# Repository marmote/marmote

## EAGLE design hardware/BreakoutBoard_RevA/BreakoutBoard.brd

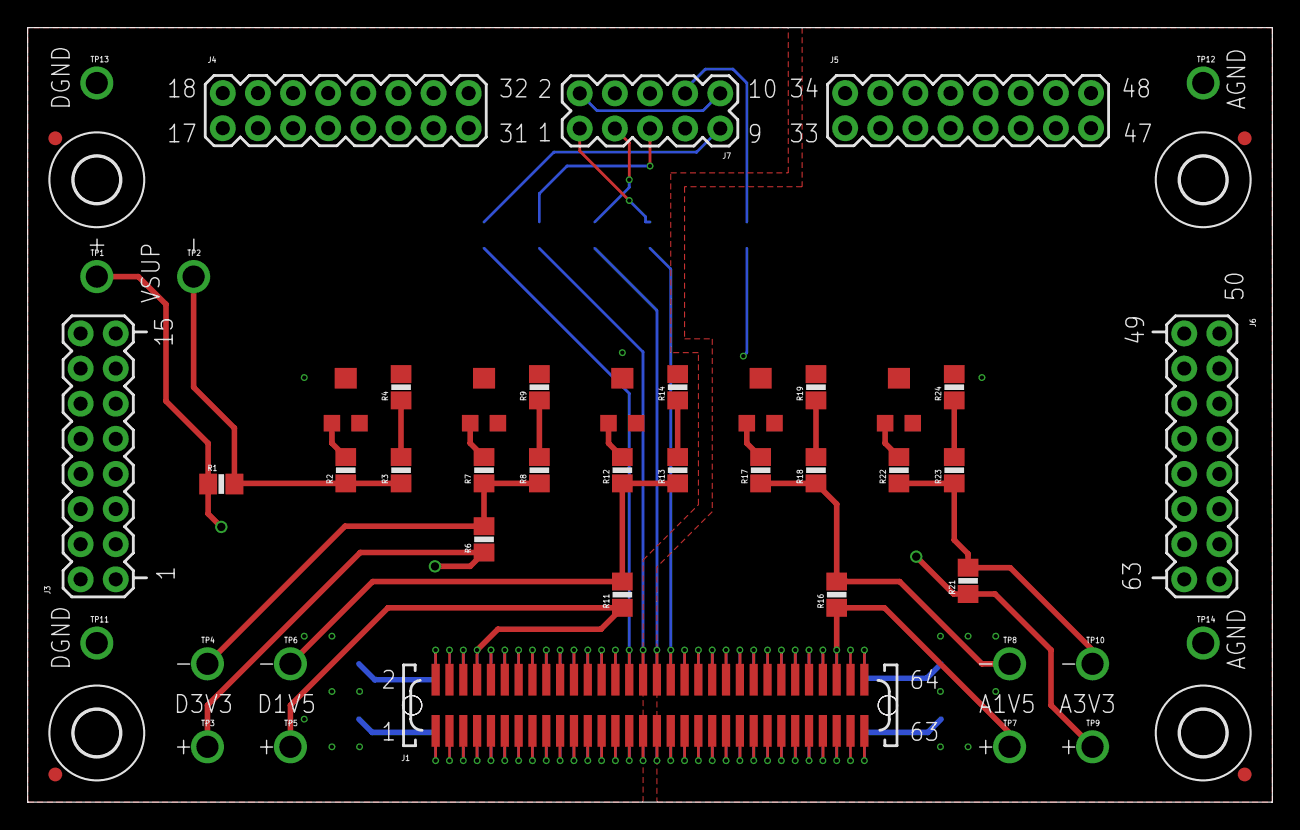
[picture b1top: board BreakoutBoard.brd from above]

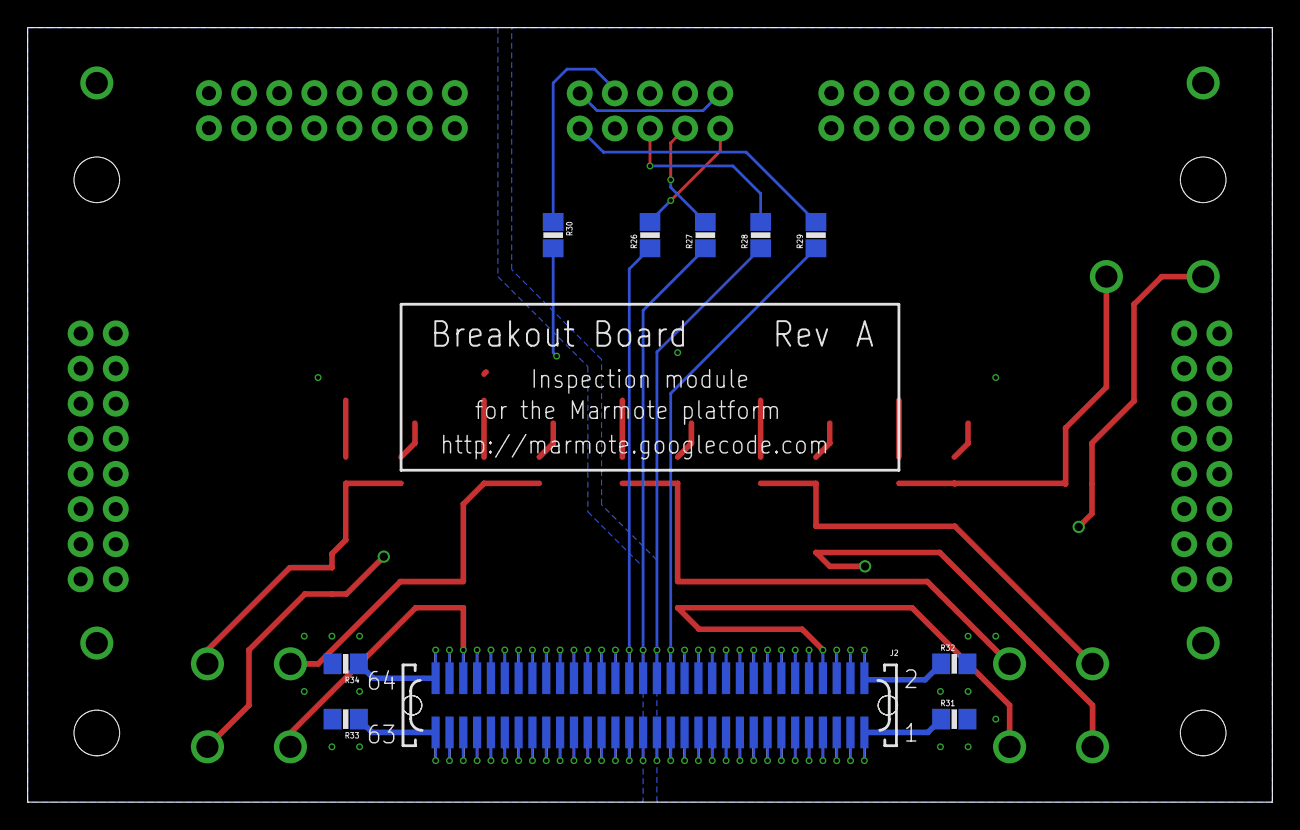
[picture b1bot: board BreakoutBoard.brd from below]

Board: 4 copper layers, 90.0 x 56.0 mm, 67 parts (10 on the bottom side), 86 nets.

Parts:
J1: CON-71436-2164-TOP; 71436-XX64
J2: CON-71439-2164; 71439-XX64-BOT
J3, J4, J5, J6: CON-2X8-RASTER; 2X16
J7: CON-HTST-105-04-D-RA; HTST-105-04-D-RA
LOGO1: LOGO-ISIS-600MIL-10MM-AU; LOGO-ISIS-10MM-GOLD
LOGO2: LOGO-VANDERBILT-600MIL-10MM-AU; LOGO-VANDERBILT-10MM-GOLD
LOGO3: LOGO-MARMOTE-600MIL-10MM-AU; LOGO-MARMOTE-10MM-GOLD
LOGO4: LOGO-MAGNIFYING-GLASS-600MIL-10MM-AU; LOGO-MAGNIFYING-GLASS-10MM-GOLD
M1, M2, M3, M4: MOUNT-HOLE3.3; 3,3
M5, M6, M7, M8: FIDUCIAL1X2; FIDUCIAL-1X2
R1, R4, R6, R9, R11, R14, R16, R19, R21, R24: 10; R0805
R2, R3, R7, R8, R12, R13, R17, R18, R22, R23, R26, R27, R28, R29, R30, R31, R32, R33, R34: 0; R0805
R5, R10, R15, R20, R25: 1000; TRIMMER-3MM
TP1, TP2, TP3, TP4, TP5, TP6: TESTPOINT-BLUE; TESTPOINT
TP7, TP8, TP9, TP10: TESTPOINT-GREEN; TESTPOINT
TP11, TP12, TP13, TP14: TESTPOINT-YELLOW; TESTPOINT

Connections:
1: J1.1, J2.1, J3.1, R31.1
2: J1.2, J2.2, J3.2, R32.1
3: J1.3, J2.3, J3.3
4: J1.4, J2.4, J3.4, R1.1, TP1.1
5: J1.5, J2.5, J3.5
6: J1.6, J2.6, J3.6, R6.1, TP3.1
7: J1.7, J2.7, J3.7
8: J1.8, J2.8, J3.8, R11.1, TP5.1
9: J1.9, J2.9, J3.9
10: J1.10, J2.10, J3.10
11: J1.11, J2.11, J3.11
12: J1.12, J2.12, J3.12
13: J1.13, J2.13, J3.13
14: J1.14, J2.14, J3.14
15: J1.15, J2.15, J3.15
16: J1.16, J2.16, J3.16
17: J1.17, J2.17, J4.1
18: J1.18, J2.18, J4.2
19: J1.19, J2.19, J4.3
20: J1.20, J2.20, J4.4
21: J1.21, J2.21, J4.5
22: J1.22, J2.22, J4.6
23: J1.23, J2.23, J4.7
24: J1.24, J2.24, J4.8
25: J1.25, J2.25, J4.9
26: J1.26, J2.26, J4.10
27: J1.27, J2.27, J4.11
28: J1.28, J2.28, J4.12
29: J1.29, J2.29, J4.13
30: J1.30, J2.30, J4.14, R29.1
31: J1.31, J2.31, J4.15
32: J1.32, J2.32, J4.16, R28.1
33: J1.33, J2.33, J5.1
34: J1.34, J2.34, J5.2, R27.1
35: J1.35, J2.35, J5.3
36: J1.36, J2.36, J5.4, R26.1
37: J1.37, J2.37, J5.5
38: J1.38, J2.38, J5.6, R30.2
39: J1.39, J2.39, J5.7
40: J1.40, J2.40, J5.8
41: J1.41, J2.41, J5.9
42: J1.42, J2.42, J5.10
43: J1.43, J2.43, J5.11
44: J1.44, J2.44, J5.12
45: J1.45, J2.45, J5.13
46: J1.46, J2.46, J5.14
47: J1.47, J2.47, J5.15
48: J1.48, J2.48, J5.16
49: J1.49, J2.49, J6.1
50: J1.50, J2.50, J6.2
51: J1.51, J2.51, J6.3
52: J1.52, J2.52, J6.4
53: J1.53, J2.53, J6.5
54: J1.54, J2.54, J6.6
55: J1.55, J2.55, J6.7
56: J1.56, J2.56, J6.8
57: J1.57, J2.57, J6.9
58: J1.58, J2.58, J6.10
59: J1.59, J2.59, J6.11
60: J1.60, J2.60, J6.12, R16.1, TP7.1
61: J1.61, J2.61, J6.13
62: J1.62, J2.62, J6.14, R21.1, TP9.1
63: J1.63, J2.63, J6.15, R33.1
64: J1.64, J2.64, J6.16, R34.1
A1V5-: R16.2, R17.1, R18.1, TP8.1
A3V3-: R21.2, R22.1, R23.1, TP10.1
AGND: R19.2, R20.2, R24.2, R25.2, R33.2, R34.2, TP12.1, TP14.1
D1V5-: R11.2, R12.1, R13.1, TP6.1
D3V3-: R6.2, R7.1, R8.1, TP4.1
DGND: J7.2, J7.10, R4.2, R5.2, R9.2, R10.2, R14.2, R15.2, R31.2, R32.2, TP11.1, TP13.1
unnamed: R7.2, R10.1
unnamed: R8.2, R9.1
unnamed: R12.2, R15.1
unnamed: R18.2, R19.1
unnamed: R17.2, R20.1
unnamed: R22.2, R25.1
unnamed: R2.2, R5.1
unnamed: R3.2, R4.1
unnamed: R13.2, R14.1
unnamed: R23.2, R24.1
TCK: J7.1, R26.2
TDI: J7.9, R29.2
TDO: J7.3, R27.2
TMS: J7.5, R28.2
TRST: J7.8, R30.1
VSUP-: R1.2, R2.1, R3.1, TP2.1

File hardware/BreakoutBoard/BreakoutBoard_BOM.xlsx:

Bill of Materials for 'Marote - Breakout Board (Rev A)'
Item # | Reference | Value | Package | Manufacturer | Manufacturer Part # | Supplier | Supplier Part # | Details | Qty per board | Unit Price | Total Qty | Total Cost
1 | J1 | CON-71436-2164 | CON-71436-2164 | Molex | 71436-2164 | Digi-Key | WM17200-ND | CONN PLUG 64POS VERT 1MM SMD | 1 | 8.6 | 3 | 25.799999999999997
2 | J2 | CON-71439-2164 | CON-71439-2164 | Molex | 71439-2164 | Digi-Key | WM17222-ND | CONN RECPT 64POS VERT 1MM SMD | 1 | 5.74 | 3 | 17.22
3 | J3* | CON-2X8 | CON-2X8 | Samtec | TSW-150-08-T-D-RA | Digi-Key | SAM1049-50-ND | CONN HEADR 100PS .100 DL R/A TIN | 1 | 4.62 | 3 | 13.86
4 | J4 | CON-HTST-105-04-D-RA | CON-HTST-105-04-D-RA | Samtec | TSW-105-08-G-D-RA | Digi-Key | SAM1037-05-ND | CONN HEADER 10POS .100 DL R/A AU | 1 | 1.66 | 3 | 4.9799999999999995
5 | R1, R4, R6, R9, R11, R14, R16, R19, R21, R24 | 10 | R0805 | Rohm | MCR10EZPF10R0 | Digi-Key | RHM10.0CRCT-ND | RES 10.0 OHM 1/8W 1% 0805 SMD | 10 | 4.2000000000000003E-2 | 30 | 1.26
5* | R1, R4, R6, R9, R11, R14, R16, R19, R21, R24 | 10 | R0805 | Rohm | MCR10ERTF20R0 | Digi-Key | RHM20.0CRCT-ND | RES 20.0 OHM 1/8W 1% 0805 SMD | 10 | 4.2000000000000003E-2 | 30 | 1.26
6 | R2, R3, R7, R8, R12, R13, R17, R18, R22, R23, R26, R27, R28, R29, R30, R31, R32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 | 0 | R0805 | Rohm | MCR10EZHJ000 | Digi-Key | RHM0.0ACT-ND | RES 0.0 OHM 1/8W 0805 SMD | 19 | 4.1000000000000002E-2 | 57 | 2.3370000000000002
7 | R5, R10, R15, R20, R25 | 1k | 3 mm Square Low-Profi le SMT | Panasonic - ECG | EVM-3WSX80B13 | Digi-Key | P3W102CT-ND | TRIMMER 1K OHM 0.15W SMD | 5 | 0.99 | 15 | 14.85
8 | TP1, TP2, TP3, TP4, TP5, TP6 | TESTPOINT | TESTPOINT-BLUE | Keystone | 5122 | Digi-Key | 5122K-ND | TEST POINT PC COMPACT T/H BLUE | 6 | 0.38 | 18 | 6.84
9 | TP7, TP8, TP9, TP10 | TESTPOINT | TESTPOINT-GREEN | Keystone | 5121 | Digi-Key | 5121K-ND | TEST POINT PC COMPACT T/H GREEN | 4 | 0.38 | 12 | 4.5600000000000005
10 | TP11, TP12, TP13, TP14 | TESTPOINT | TESTPOINT-YELLOW | Keystone | 5009 | Digi-Key | 5009K-ND | TEST POINT PC COMPACT .063"D YLW | 4 | 0.36 | 12 | 4.32
11 | M1,M2,M3,M4 | STANDOFF | Aluminum | Keystone | 8401 | Digi-Key | 8401K-ND | STDOFF HEX M/F 4-40 .500"L ALUM | 4 | 0.71699999999999997 | 12 | 8.6039999999999992
 |  |  |  |  |  |  |  |  |  |  |  | 105.89100000000001
*Note: The part for J3 is a 2x50 header that needs to be cut into 2x8 pieces by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
 | Number of boards: | 3

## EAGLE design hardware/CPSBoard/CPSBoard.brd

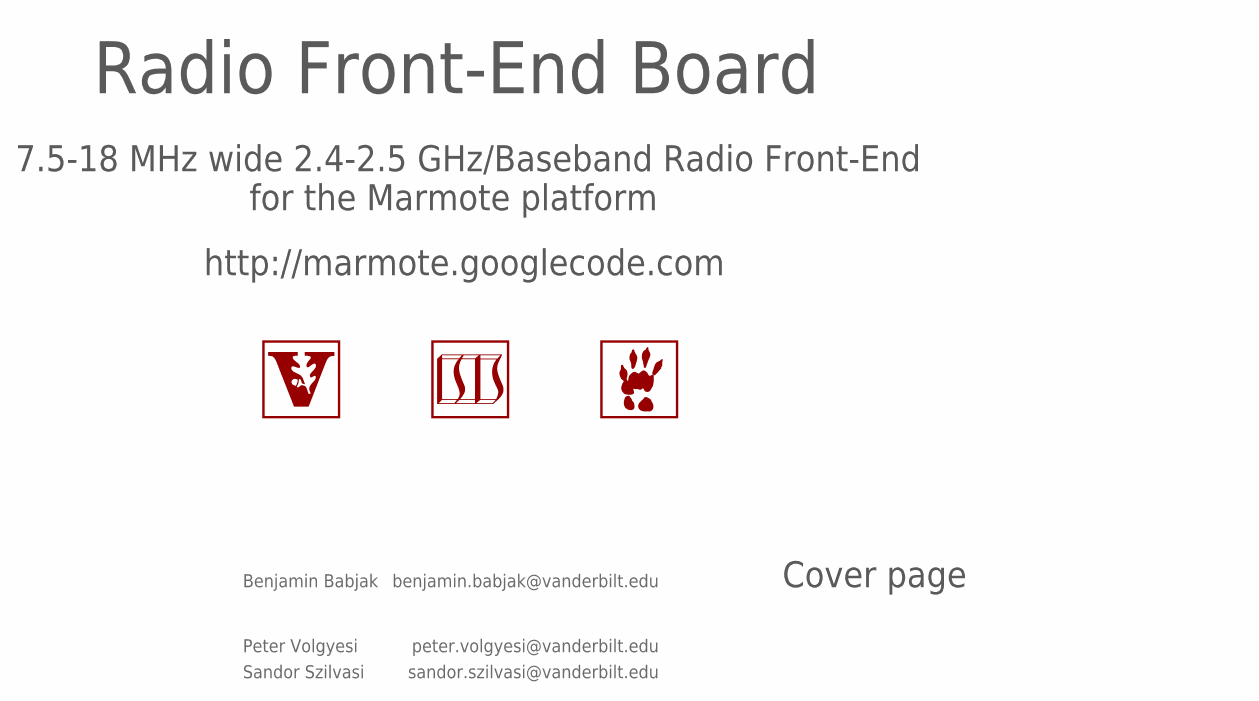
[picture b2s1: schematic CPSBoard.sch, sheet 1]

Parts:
LOGO1: LOGO-ISIS-600MIL-10MM-AU; LOGO-ISIS-10MM-GOLD
LOGO2: LOGO-MARMOTE-600MIL-10MM-AU; LOGO-MARMOTE-10MM-GOLD
LOGO3: LOGO-VANDERBILT-600MIL-10MM-AU; LOGO-VANDERBILT-10MM-GOLD

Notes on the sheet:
7.5-18 MHz wide 2.4-2.5 GHz/Baseband Radio Front-End
http://marmote.googlecode.com
for the Marmote platform

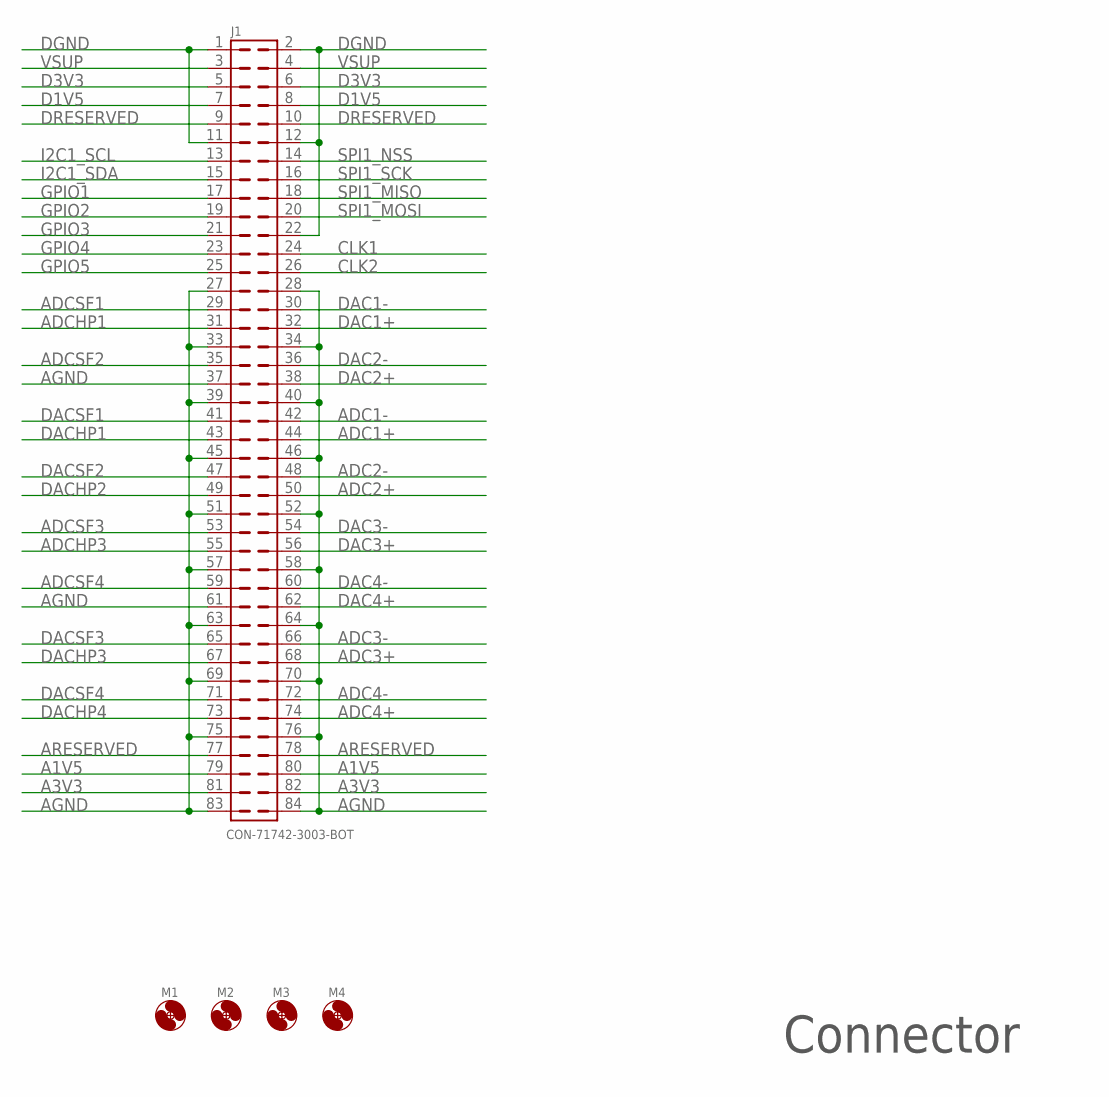
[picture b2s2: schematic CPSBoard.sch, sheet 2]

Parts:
J1: CON-71742-3003-BOT; 71742-3003-BOT
M1, M2, M3, M4: MOUNT-HOLE3.3; 3,3

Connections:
A1V5: J1.79, J1.80
A3V3: J1.81, J1.82; also elsewhere on the board
ADC1+: J1.44
ADC1-: J1.42
ADC2+: J1.50
ADC2-: J1.48
ADC3+: J1.68
ADC3-: J1.66
ADC4+: J1.74
ADC4-: J1.72
ADCHP1: J1.31
ADCHP3: J1.55
ADCSF1: J1.29
ADCSF2: J1.35
ADCSF3: J1.53
ADCSF4: J1.59
AGND: J1.27, J1.28, J1.33, J1.34, J1.37, J1.39, J1.40, J1.45, J1.46, J1.51, J1.52, J1.57, J1.58, J1.61, J1.63, J1.64, J1.69, J1.70, J1.75, J1.76, J1.83, J1.84; also elsewhere on the board
ARESERVED: J1.77, J1.78
CLK1: J1.24
CLK2: J1.26
D1V5: J1.7, J1.8
D3V3: J1.5, J1.6; also elsewhere on the board
DAC1+: J1.32
DAC1-: J1.30
DAC2+: J1.38
DAC2-: J1.36
DAC3+: J1.56
DAC3-: J1.54
DAC4+: J1.62
DAC4-: J1.60
DACHP1: J1.43
DACHP2: J1.49
DACHP3: J1.67
DACHP4: J1.73
DACSF1: J1.41
DACSF2: J1.47
DACSF3: J1.65
DACSF4: J1.71
DGND: J1.1, J1.2, J1.11, J1.12, J1.22; also elsewhere on the board
DRESERVED: J1.9, J1.10
GPIO1: J1.17; also elsewhere on the board
GPIO2: J1.19; also elsewhere on the board
GPIO3: J1.21; also elsewhere on the board
GPIO4: J1.23; also elsewhere on the board
GPIO5: J1.25; also elsewhere on the board
I2C1_SCL: J1.13; also elsewhere on the board
I2C1_SDA: J1.15; also elsewhere on the board
SPI1_MISO: J1.18; also elsewhere on the board
SPI1_MOSI: J1.20; also elsewhere on the board
SPI1_NSS: J1.14; also elsewhere on the board
SPI1_SCK: J1.16; also elsewhere on the board
VSUP: J1.3, J1.4

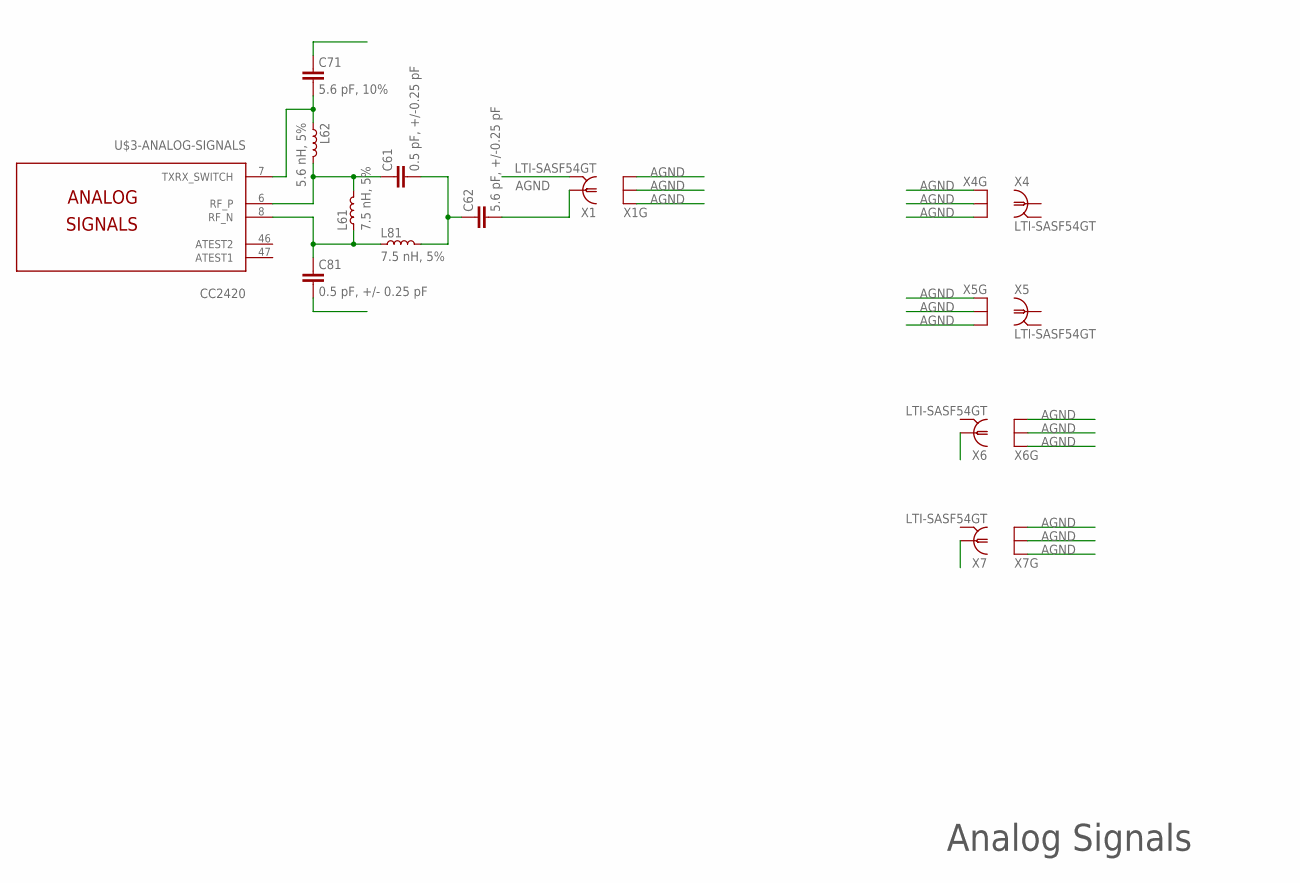
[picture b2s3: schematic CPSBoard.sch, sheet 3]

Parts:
C61: 0.5 pF, +/-0.25 pF; C0402
C62: 5.6 pF, +/-0.25 pF; C0402
C71: 5.6 pF, 10%; C0402
C81: 0.5 pF, +/- 0.25 pF; C0402
L61, L81: 7.5 nH, 5%; C0402
L62: 5.6 nH, 5%; C0402
U$3: CC2420; VQFN-48
X1, X4, X5, X6, X7: LTI-SASF54GT

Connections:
AGND: X1.2 (GND), X1.3 (GND), X1.4 (GND), X1.5 (GND), X4.3 (GND), X4.4 (GND), X4.5 (GND), X5.3 (GND), X5.4 (GND), X5.5 (GND), X6.3 (GND), X6.4 (GND), X6.5 (GND), X7.3 (GND), X7.4 (GND), X7.5 (GND); also elsewhere on the board
GND: X4.2 (GND), X5.2 (GND), X6.2 (GND), X7.2 (GND)
unnamed: C71.2, L62.1, U$3.7 (TXRX_SWITCH)
unnamed: C61.1, L61.2, L62.2, U$3.6 (RF_P)
unnamed: C62.2, X1.1
unnamed: C81.1, L61.1, L81.1, U$3.8 (RF_N)
unnamed: C61.2, C62.1, L81.2

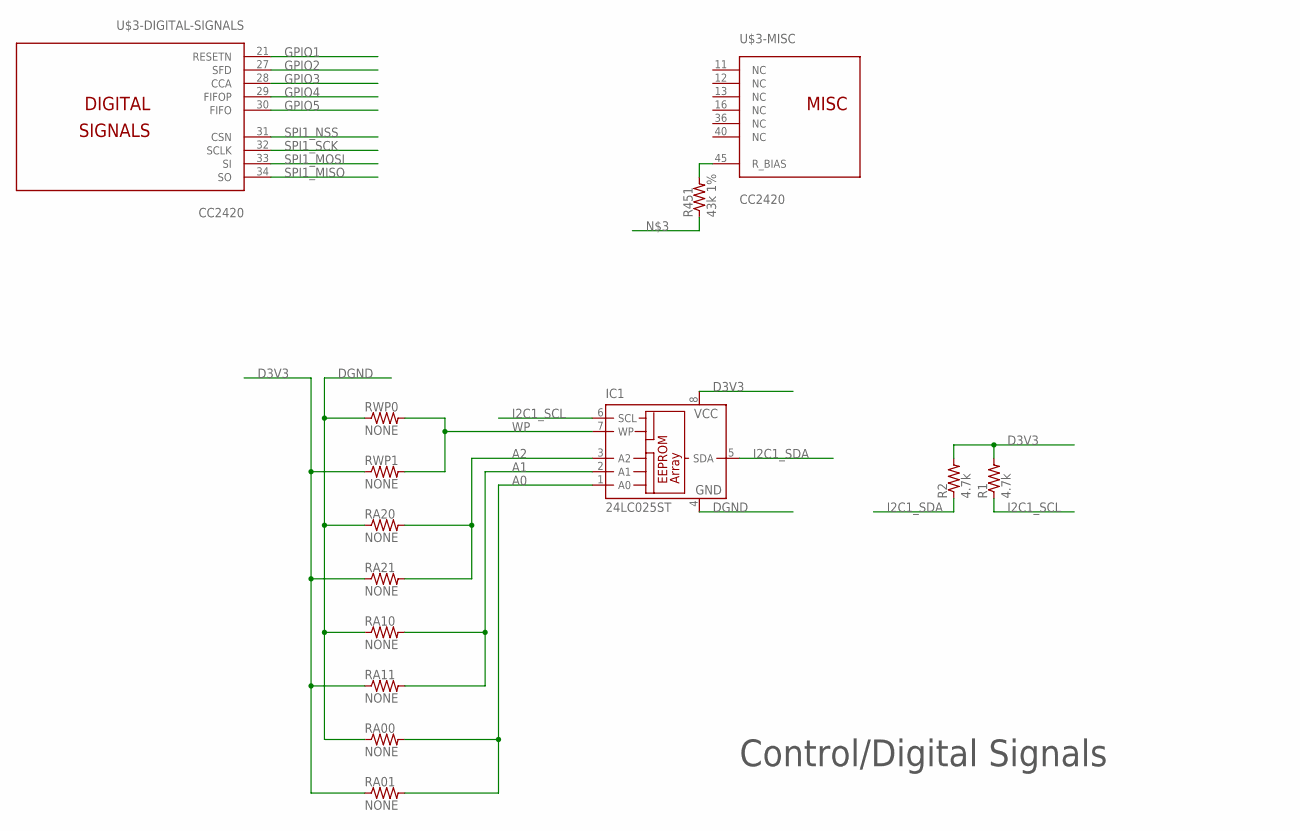
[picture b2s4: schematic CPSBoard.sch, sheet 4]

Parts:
IC1: 24LC025ST; TSSOP8
R1, R2: 4.7k; R0402
R451: 43k 1%; R0402
RA00, RA01, RA10, RA11, RA20, RA21: NONE; R0402
RWP0, RWP1: NONE; R0402
U$3: CC2420; VQFN-48

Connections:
A0: IC1.1 (A0), RA00.2, RA01.2
A1: IC1.2 (A1), RA10.2, RA11.2
A2: IC1.3 (A2), RA20.2, RA21.2
D3V3: IC1.8 (VCC), R1.2, R2.2, RA01.1, RA11.1, RA21.1, RWP1.1; also elsewhere on the board
DGND: IC1.4 (GND), RA00.1, RA10.1, RA20.1, RWP0.1; also elsewhere on the board
GPIO1: U$3.21 (RESETN); also elsewhere on the board
GPIO2: U$3.27 (SFD); also elsewhere on the board
GPIO3: U$3.28 (CCA); also elsewhere on the board
GPIO4: U$3.29 (FIFOP); also elsewhere on the board
GPIO5: U$3.30 (FIFO); also elsewhere on the board
I2C1_SCL: IC1.6 (SCL), R1.1; also elsewhere on the board
I2C1_SDA: IC1.5 (SDA), R2.1; also elsewhere on the board
unnamed: R451.2, U$3.45 (R_BIAS)
SPI1_MISO: U$3.34 (SO); also elsewhere on the board
SPI1_MOSI: U$3.33 (SI); also elsewhere on the board
SPI1_NSS: U$3.31 (CSN); also elsewhere on the board
SPI1_SCK: U$3.32 (SCLK); also elsewhere on the board
WP: IC1.7 (WP), RWP0.2, RWP1.2

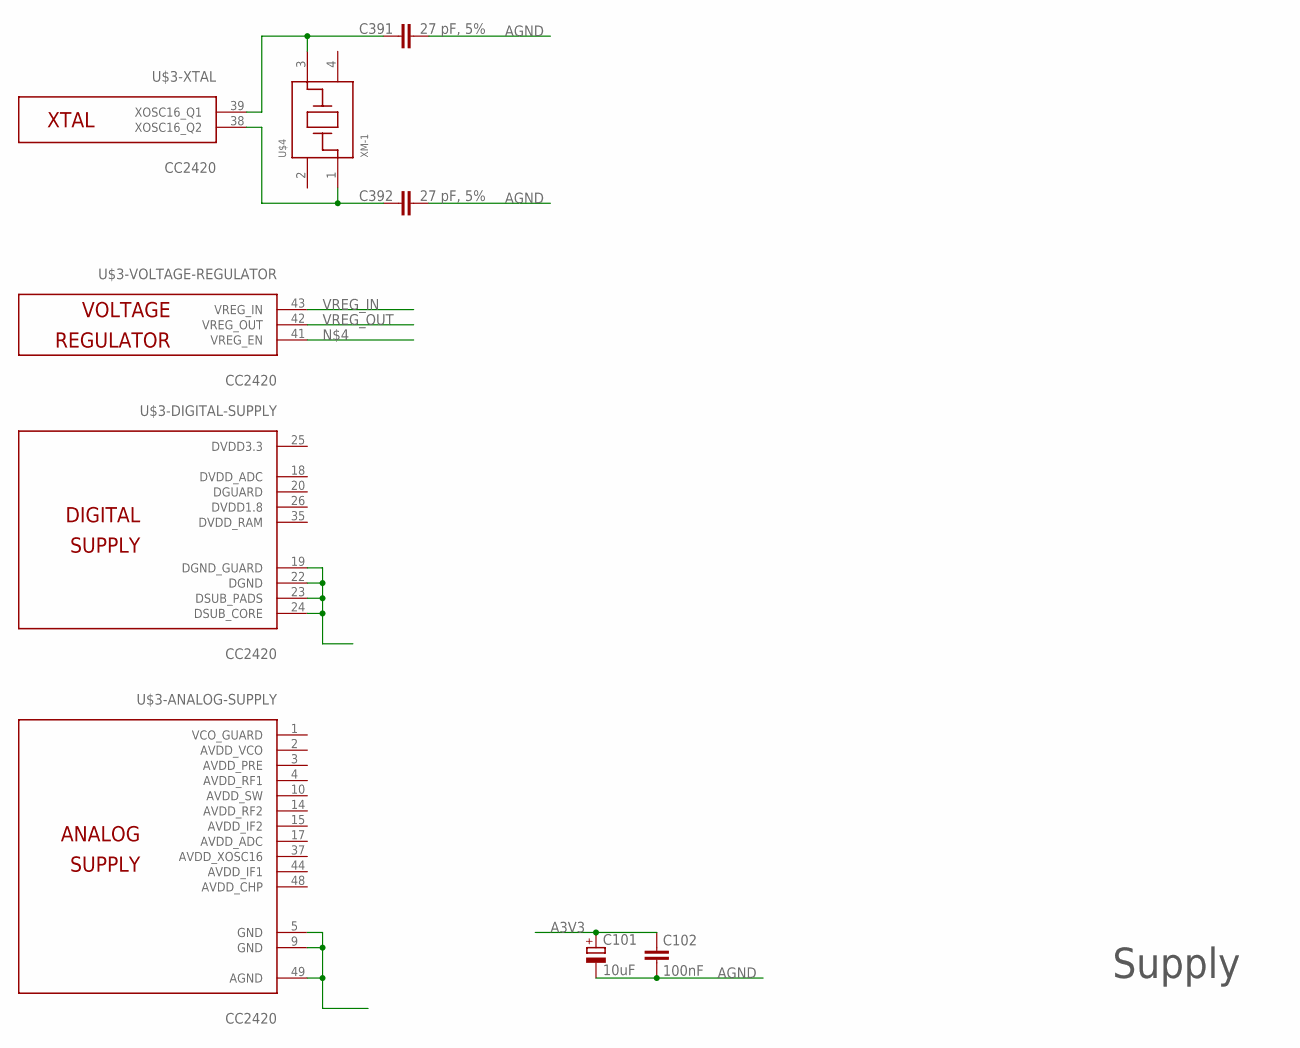
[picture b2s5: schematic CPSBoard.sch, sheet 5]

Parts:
C101: 10uF; CPOL2012
C102: 100nF; C0402
C391, C392: 27 pF, 5%; C0402
U$3: CC2420; VQFN-48
U$4: XM-1; XM-1-FOOTPRINT

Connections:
A3V3: C101.+, C102.1; also elsewhere on the board
AGND: C101.-, C102.2, C391.2, C392.2, U$3.5 (GND), U$3.9 (GND), U$3.49 (AGND); also elsewhere on the board
DSUB_CORE: U$3.19 (DGND_GUARD), U$3.22 (DGND), U$3.23 (DSUB_PADS), U$3.24 (DSUB_CORE)
unnamed: C391.1, U$3.39 (XOSC16_Q1), U$4.3
unnamed: C392.1, U$3.38 (XOSC16_Q2), U$4.1
VREG_IN: U$3.43 (VREG_IN)
VREG_OUT: U$3.42 (VREG_OUT)

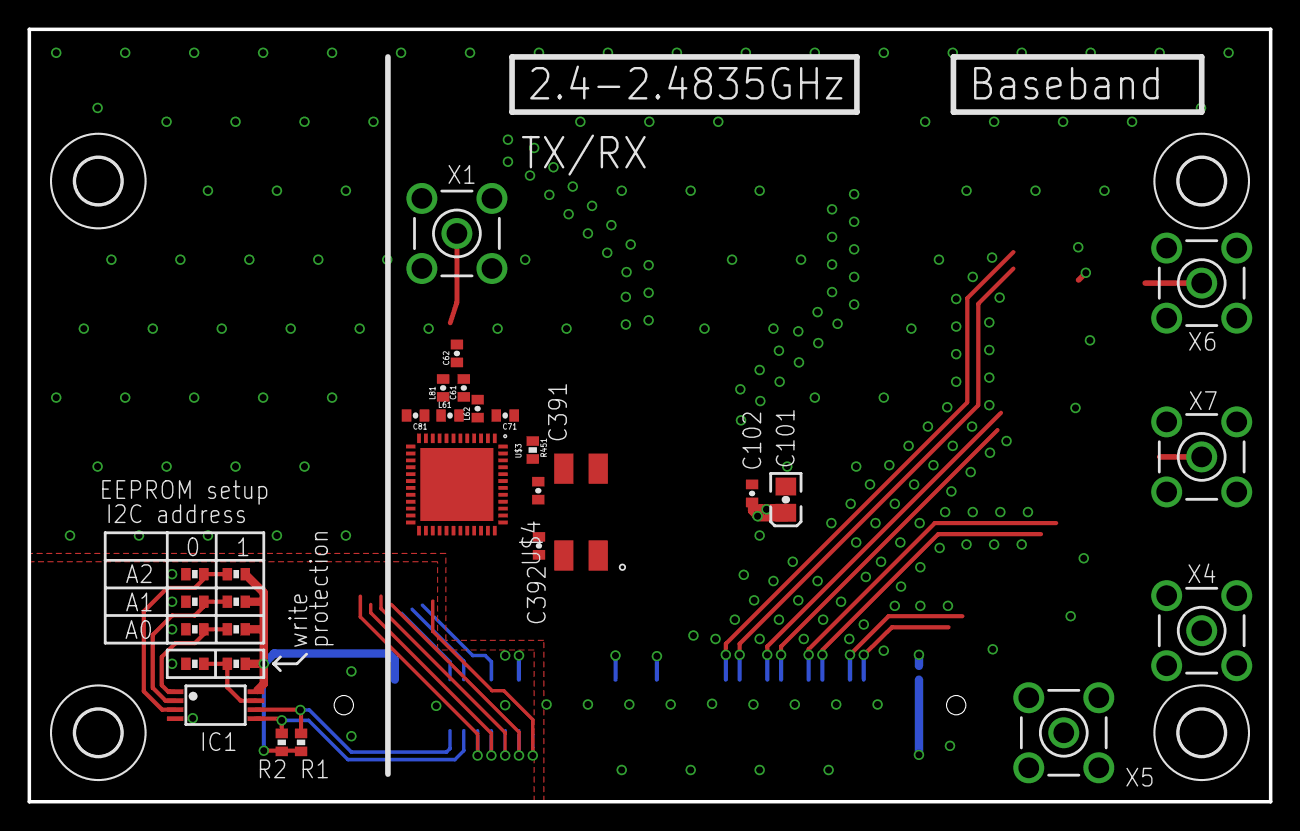
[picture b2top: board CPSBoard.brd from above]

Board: 4 copper layers, 90.0 x 56.0 mm, 38 parts (1 on the bottom side), 34 nets.

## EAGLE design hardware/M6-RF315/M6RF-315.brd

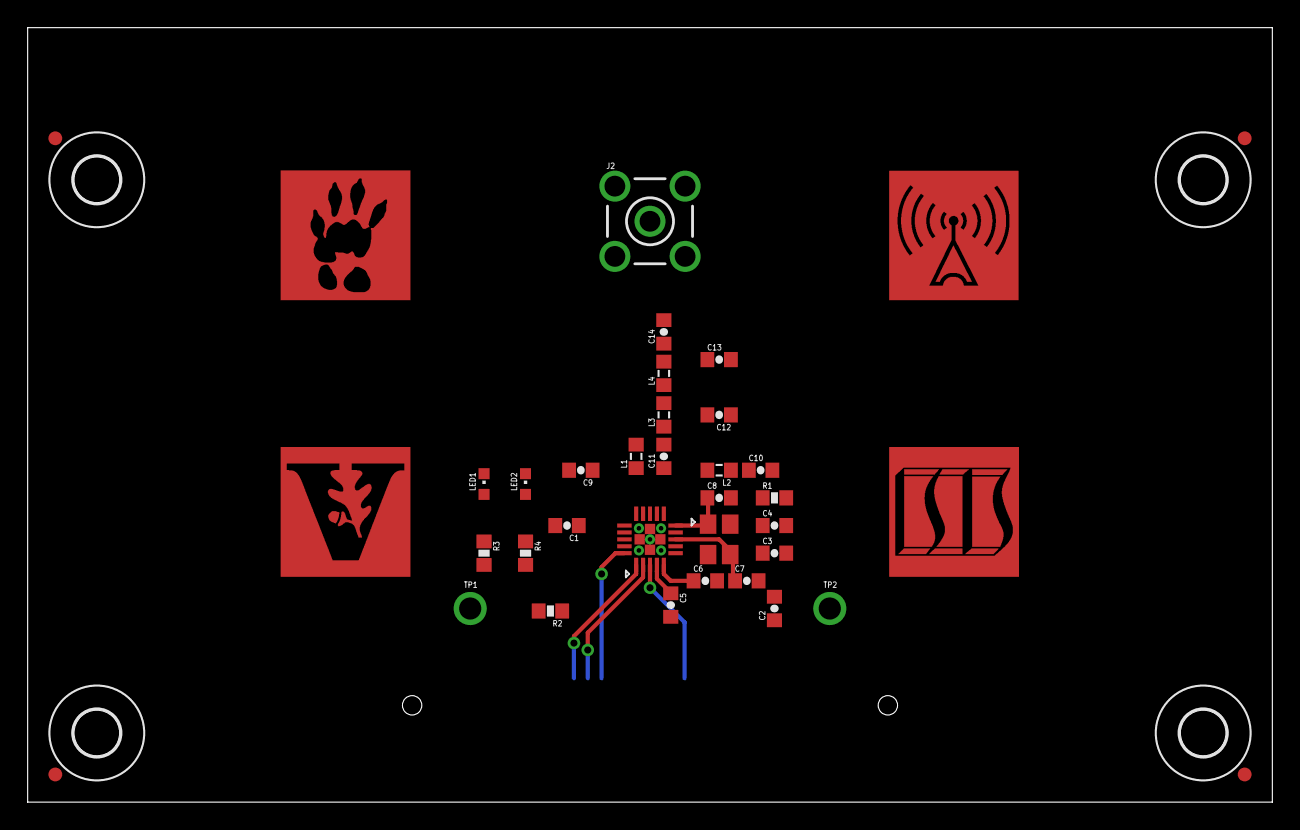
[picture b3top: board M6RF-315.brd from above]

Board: 2 copper layers, 90.0 x 56.0 mm, 42 parts (1 on the bottom side), 29 nets.

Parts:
C1, C2, C3, C4, C5, C6: 100nF; C0603
C7, C12: 12pF; C0603
C8: 15pF; C0603
C9: 6.8 pF; C0603
C10, C14: 220pF; C0603
C11, C13: 6.8pF; C0603
J1: CON-71439-2164; 71439-XX64-BOT
J2: CON-SMA-VERT; SMA-VERT
L1, L2, L4: 33nH; L0603
L3: 18nH; L0603
LED1, LED2: LED0603
LOGO1: LOGO-ISIS-600MIL-10MM-CU; LOGO-ISIS-10MM-COPPER
LOGO2: LOGO-MARMOTE-600MIL-10MM-CU; LOGO-MARMOTE-10MM-COPPER
LOGO3: LOGO-VANDERBILT-600MIL-10MM-CU; LOGO-VANDERBILT-10MM-COPPER
M1, M2, M3, M4: MOUNT-HOLE3.3; 3,3
M5, M6, M7, M8: FIDUCIAL1X2; FIDUCIAL-1X2
R1: 56k; R0603
R2: 100k; R0603
R3: 500; R0603
R4: 130; R0603
TP1, TP2: TESTPOINT-RED; TESTPOINT
U1: CC1101RTKR; QFN-20
U$3: LOGO-RADIO-2-600MIL-10MM-CU; LOGO-RADIO-2-10MM-COPPER
X1: NX3225GA

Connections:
A1V5: J1.59, J1.60
A3V3: C1.1, C2.1, C3.1, C4.1, J1.61, J1.62, U1.9, U1.11, U1.14, U1.15
AGND: C1.2, C2.2, C3.2, C4.2, C9.1, C10.2, C12.2, C13.2, J1.55, J1.56, J1.63, J1.64, J2.2, R1.2, U1.16
D1V5: J1.7, J1.8
D3V3: C5.1, J1.5, J1.6, R2.2, R3.2, R4.2, U1.4, U1.18
DGND: C5.2, C6.2, C7.2, C8.2, J1.1, J1.2, J1.11, J1.12, J1.18, J1.28, J1.40, U1.19, X1.2, X1.4
GND: J2.3, J2.4, J2.5
unnamed: LED1.A, R3.1
unnamed: C12.1, L3.2, L4.1
unnamed: R1.1, U1.17
unnamed: C6.1, U1.5
unnamed: C8.1, U1.10, X1.1
unnamed: C7.1, U1.8, X1.3
unnamed: C11.1, L2.2, U1.12
unnamed: C9.2, L1.1, U1.13
unnamed: C11.2, L1.2, L3.1
unnamed: C13.1, C14.1, L4.2
unnamed: C14.2, J2.1
unnamed: C10.1, L2.1
unnamed: LED2.A, R4.1
PA10: J1.36, TP1.1, U1.6
PB4: J1.38, TP2.1, U1.3
PB6: J1.14, LED2.C
PB7: J1.16, LED1.C
SPI1_MISO: J1.24, U1.2
SPI1_MOSI: J1.26, U1.20
SPI1_NSS: J1.20, R2.1, U1.7
SPI1_SCK: J1.22, U1.1
VSUP: J1.3, J1.4

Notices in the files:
parts and their libraries:
CPSBoard: Copyright © 2012 Vanderbilt University, ISIS
